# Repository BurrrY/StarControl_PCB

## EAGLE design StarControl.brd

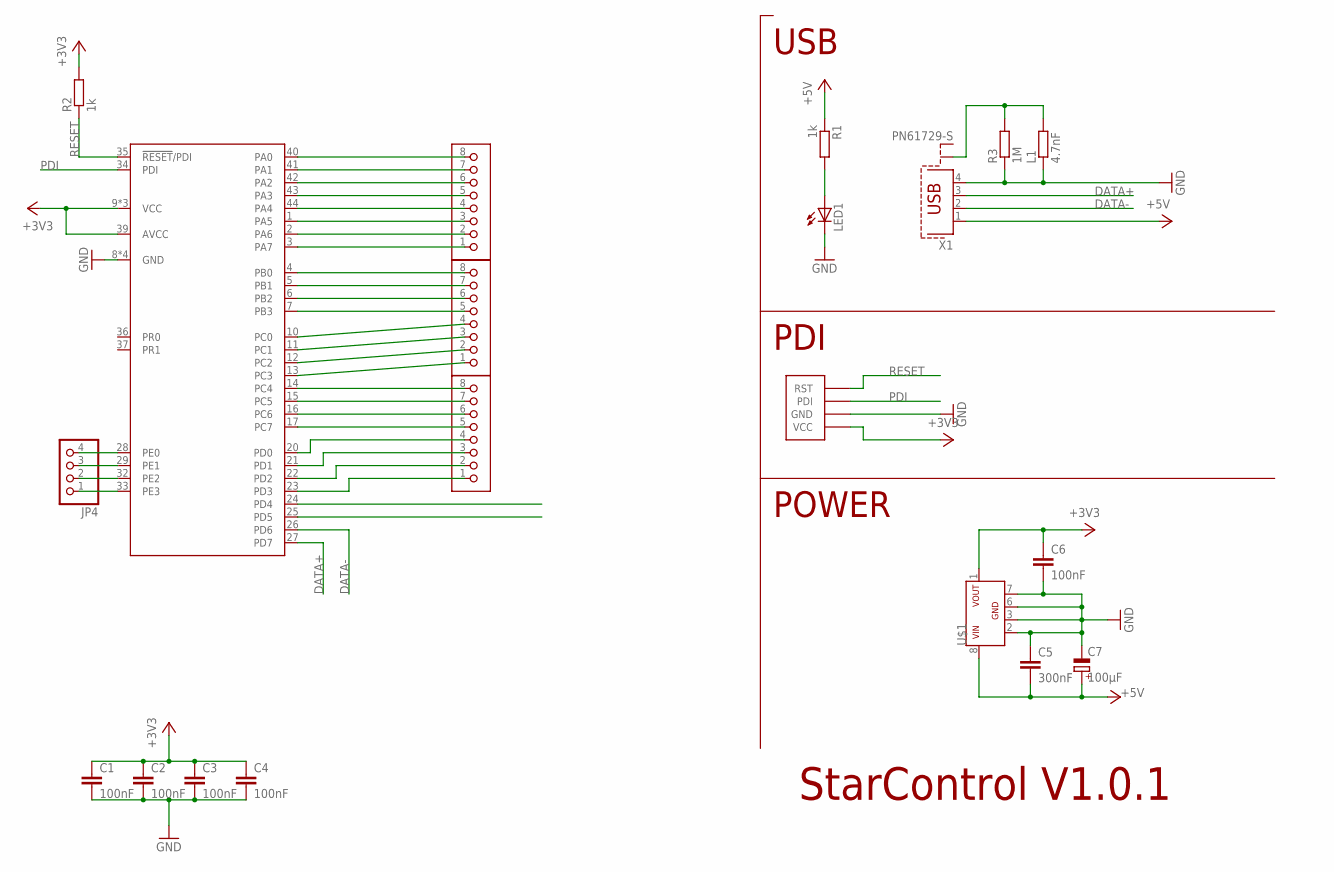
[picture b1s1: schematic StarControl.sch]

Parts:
C1, C2, C3, C4: 100nF; C0603K
C5: 300nF; C1206
C6: 100nF; C1206
C7: 100µF; E2,5-5
JP4: PINHD-1X4; 1X04
L1: 4.7nF; R0805
LED1: LED3MM
R1: 1k; R1206
R2: 1k; R0805
R3: 1M; R0805
U1: ATXMEGA16C4-AU; TQFP-44A-44
U$1: L78L33ACD13T; SO-08
U$2: PDI-4PIN; 1X04
U$3, U$4, U$5: AKL059-08
X1: PN61729-S

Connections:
+3V3: C1.1, C2.1, C3.1, C4.1, C6.1, R2.2, U1.9 (VCC), U1.19 (VCC), U1.31 (VCC), U1.39 (AVCC), U$1.1, U$2.4 (VCC)
+5V: C5.2, C7.+, R1.1, U$1.8, X1.1
DATA+: U1.27 (PD7), X1.3
DATA-: U1.26 (PD6), X1.2
GND: C1.2, C2.2, C3.2, C4.2, C5.1, C6.2, C7.-, L1.1, LED1.K (C), R3.1, U1.8 (GND), U1.18 (GND), U1.30 (GND), U1.38 (GND), U$1.2, U$1.3, U$1.6, U$1.7, U$2.2 (GND), X1.4
unnamed: JP4.4, U1.28 (PE0)
unnamed: JP4.3, U1.29 (PE1)
unnamed: JP4.2, U1.32 (PE2)
unnamed: JP4.1, U1.33 (PE3)
unnamed: U1.4 (PB0), U$5.8
unnamed: U1.5 (PB1), U$5.7
unnamed: U1.6 (PB2), U$5.6
unnamed: U1.7 (PB3), U$5.5
unnamed: U1.40 (PA0), U$4.8
unnamed: U1.41 (PA1), U$4.7
unnamed: U1.42 (PA2), U$4.6
unnamed: U1.43 (PA3), U$4.5
unnamed: U1.44 (PA4), U$4.4
unnamed: U1.1 (PA5), U$4.3
unnamed: U1.2 (PA6), U$4.2
unnamed: U1.3 (PA7), U$4.1
unnamed: U1.10 (PC0), U$5.4
unnamed: U1.11 (PC1), U$5.3
unnamed: U1.12 (PC2), U$5.2
unnamed: U1.13 (PC3), U$5.1
unnamed: U1.17 (PC7), U$3.5
unnamed: U1.16 (PC6), U$3.6
unnamed: U1.15 (PC5), U$3.7
unnamed: U1.14 (PC4), U$3.8
unnamed: U1.20 (PD0), U$3.4
unnamed: U1.21 (PD1), U$3.3
unnamed: U1.22 (PD2), U$3.2
unnamed: U1.23 (PD3), U$3.1
unnamed: LED1.A, R1.2
unnamed: L1.2, R3.2, X1.S1
PDI: U1.34 (PDI), U$2.1 (PDI)
RESET: R2.1, U1.35 (!RESET!/PDI), U$2.3 (RST)

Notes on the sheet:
PDI
POWER
USB
StarControl V1.0.1

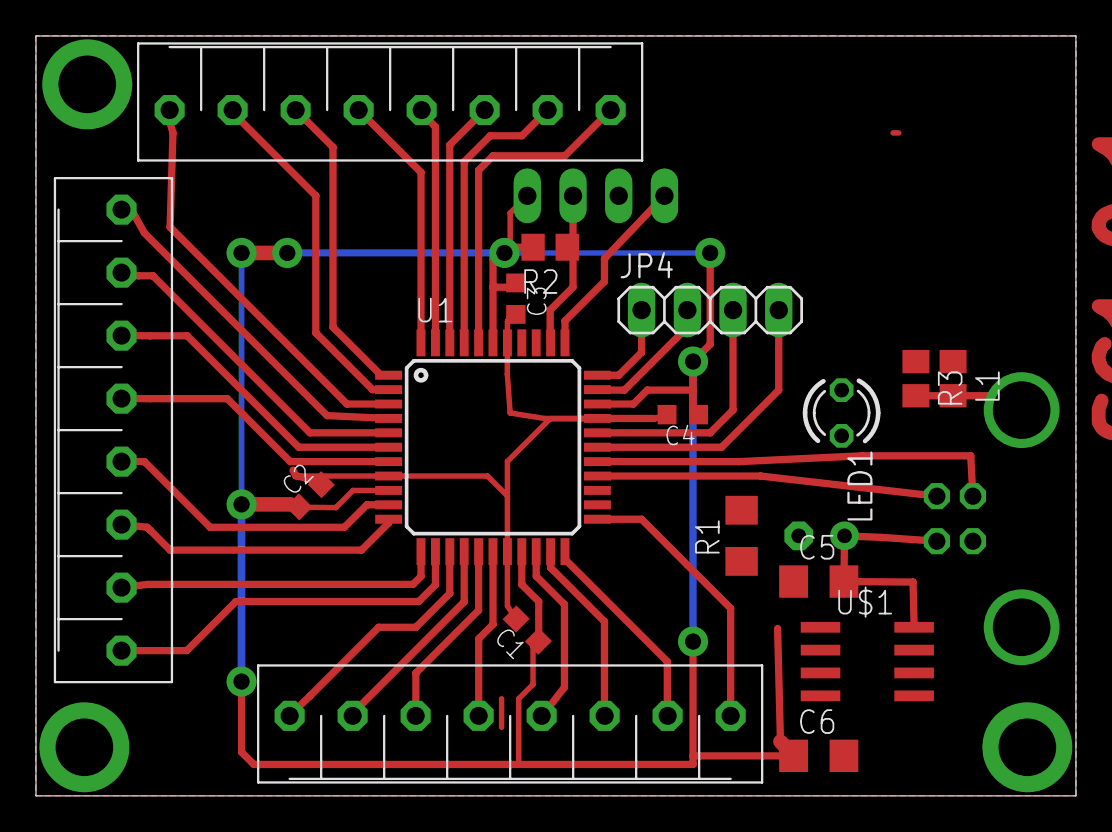
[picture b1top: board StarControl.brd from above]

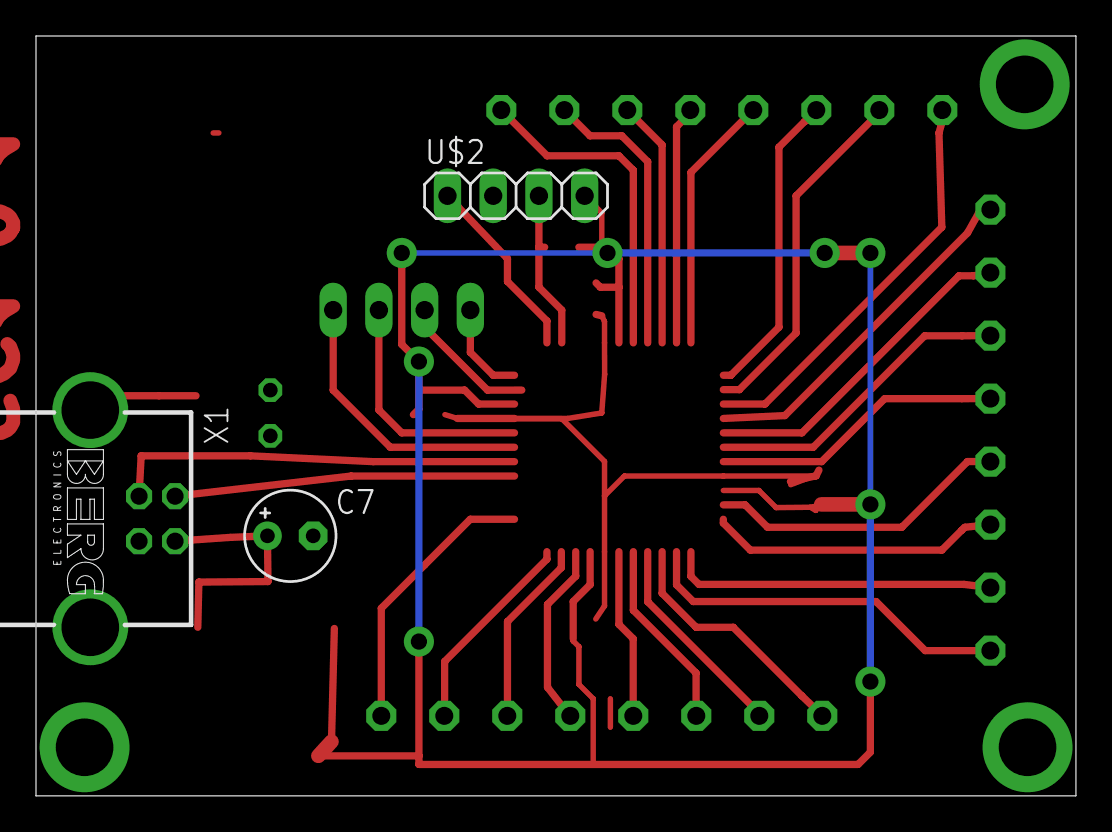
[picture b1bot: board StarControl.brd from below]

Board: 2 copper layers, 57.8 x 42.2 mm, 20 parts (3 on the bottom side), 37 nets.
